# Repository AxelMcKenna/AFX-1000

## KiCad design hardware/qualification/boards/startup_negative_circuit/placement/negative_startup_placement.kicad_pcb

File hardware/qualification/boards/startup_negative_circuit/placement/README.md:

# NF03P native placement and routing study

This actual KiCad board places all231 parts from the sealed NF03C circuit on a
149×39 mm, four-layer PCB. It is a receiving design study, with no fabrication
release. `generated/native-pcb.json` records exact physical-pad/net parity,
including the four intentionally unconnected physical TLP4590AF lead3 pads.

The N12 force components are grouped on the left and N19 on the right. Deep
module/film parts are anchored explicitly. Thirty-two actual AUX-powered ICs
have assigned rear-side0603 bypass capacitors, with at most1.543 mm projected
pad separation before routing. Actual return/via inductance remains unaccepted.
The remaining generic shunt/timing/filter parts and physical connectors require
real selections and complete package/process review.

Six DCU0008A footprints use TI's actual example land instead of the generic
library's incompatible pad spacing. A separate cosmetic footprint variant
removes external silk triangles where they overlapped neighboring silk; it
preserves all electrical geometry. These changes are recorded with original and
replacement hashes. No DRC exclusions or ignored checks are used. The fresh
private `routing/connectivity-silk/input.kicad_pcb` has zero native violations,
but499 unrouted connections before the routing experiment.

The intended world frame is X=172+u, Z=3.5+v, Y=180.5−w, with nativeu/v on the
board and positivew outward from the component-front face. FR4 lies behind
that face; a1.76 mm maximum FR4 thickness and1.0 mm rear assembly envelope reach
Y183.26, below the Y183.8 lid seat. The receiving board spans X172..321 and
Z3.5..42.5. This arithmetic does not establish complete fit: actual bodies,
tails, mates, wire bends, bosses, mounting and floor-port blockage require the
separate whole-unit assembly review. There are no implemented board mounts.

`route_io.py` exports immutable per-candidate DSN/PCB/project files and imports
Specctra sessions while checking all component positions, sides, values and
pad nets. The In1.Cu AGND plane is a connectivity proposal. Default0.2 mm signal
tracks do not qualify the negative force path, Kelvin sensing or quiet returns;
these require explicit copper resistance, current and noise review after native
KiCad DRC. Existing E28 source/output Kelvin and force connections are separate
integration work.

The first FreeRouting native executable failed on missing Graal serialization
support; its log/rejection is retained under the private routing candidate.
The Java25/JAR fallback runs on the same bound DSN with a separate private
profile, analytics/API/MCP disabled. Router results require import and fresh
KiCad checks before adoption.

The newer [NF04R readiness successor](../ready_integration/README.md) adds an
output buffer and bypass and changes spare-gate wiring. This231-part board does
**not** yet implement that233-part circuit. Standalone ARM/START generation,
module initial-power margin, E28 integration, physical wiring, protected endpoint
voltage, startup/fault behavior and installed cooling remain open.

The SVG/PDF under `generated/` show actual footprint placement. They are review
drawings, not manufacturing outputs. All physical and release flags remain false.

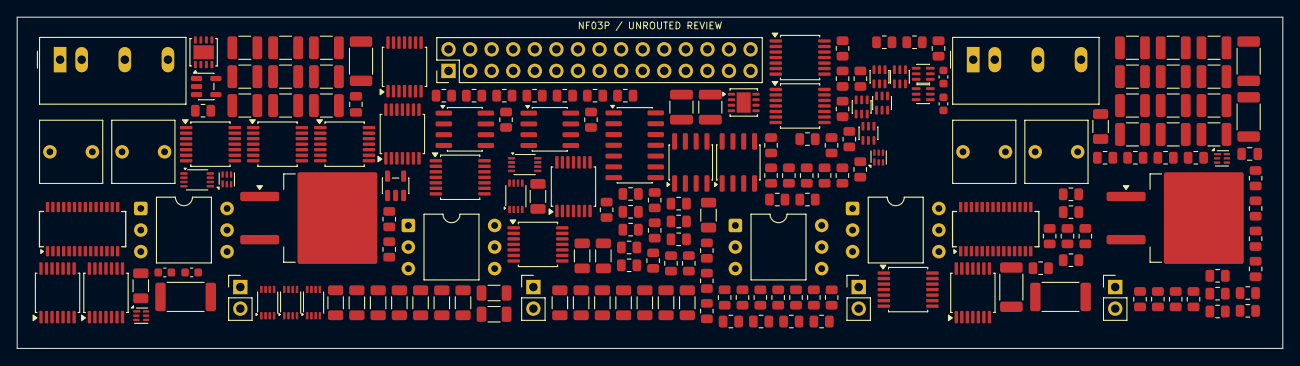
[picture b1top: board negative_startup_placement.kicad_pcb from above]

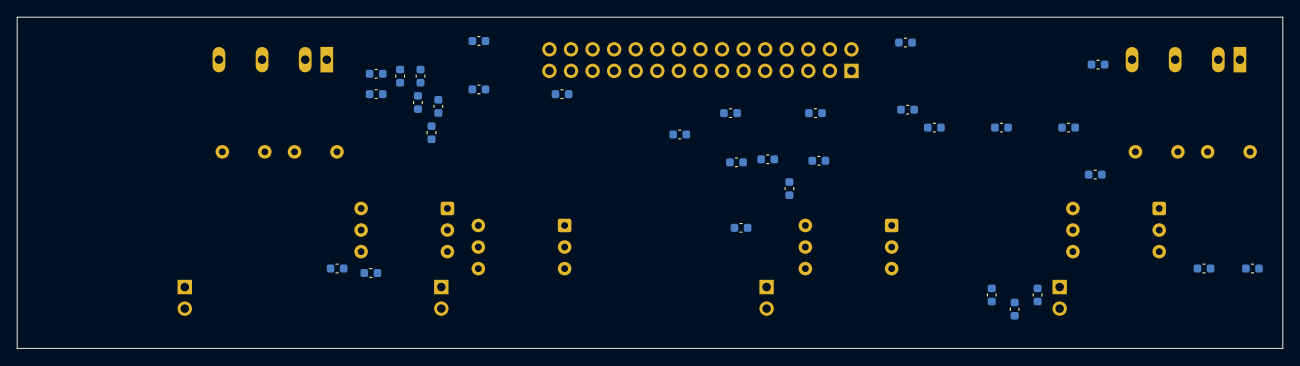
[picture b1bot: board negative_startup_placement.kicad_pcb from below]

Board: 4 copper layers, 149.0 x 39.0 mm, 231 parts (32 on the bottom side), 186 nets, no tracks yet.

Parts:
C1: 56nF C0G COMPLETE +/-10% RECEIVING; Capacitor_SMD__C_0805_2012Metric
C2: 33nF C0G COMPLETE +/-10% RECEIVING; Capacitor_SMD__C_0805_2012Metric
C3, C12, C39, C55, C56, C57, C58, C59, C60, C61, C62, C63, C64, C65, C66, C67, C68, C69, C70, C71, C72, C73, C74, C75, C76, C77, C78, C79, C80, C81, C82, C83, C84, C85, C86, C87: 100nF 50V X7R10% C0603C104K5RACTU - bypass effect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; Capacitor_SMD__C_0603_1608Metric
C4, C31: 10uF 25V X7R MODULE INPUT FILTER/EFFECTIVE/INRUSH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; Capacitor_SMD__C_1206_3216Metric
C5, C32: 1uF 50V X7R MODULE OUTPUT FILTER/EFFECTIVE HOLD; Capacitor_SMD__C_1206_3216Metric
C6, C33: 1uF 25V X7R LTC4261 local VIN effective HOLD; Capacitor_SMD__C_1206_3216Metric
C7, C9, C11, C13, C34, C36, C38, C40: 100nF 25V C0G C1206C104J3GACTU; Capacitor_SMD__C_1206_3216Metric
C8, C10, C35, C37: 10nF 50V C0G COMPLETE10% TIMING RECEIVING; Capacitor_SMD__C_1206_3216Metric
C14, C15, C16, C17, C18, C19, C20, C21, C22, C23, C24, C25, C41, C42, C43, C44, C45, C46, C47, C48, C49: 100nF 50V C0G C1210C104J5GACTU - COMPLETE10% RAMP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; Capacitor_SMD__C_1210_3225Metric
C26, C27, C50, C51: 2.2uF 63V PET5% MKS2C042201K00JSSD - COMPLETE10% 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; Capacitor_THT__C_Rect_L7.2mm_W7.2mm_P5.00mm_FKS2_FKP2_MKS2_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
C28, C30, C52, C54: 47nF 50V C0G C1206C473J5GACTU; Capacitor_SMD__C_1206_3216Metric
C29, C53: 100nF 50V C0G C1210C104J5GACTU; Capacitor_SMD__C_1210_3225Metric
J1: NEW NF03C CONTROL/KELVIN INTERFACE - physical con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; Connector_PinHeader_2.54mm__PinHeader_2x15_P2.54mm_Vertical
J2: N19 NEW FORCE IN/OUT - connector and harness unse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; Connector_PinHeader_2.54mm__PinHeader_1x02_P2.54mm_Vertical
J3: N19 E28 BANK GATE/COMMON CLAMP - physical interfa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; Connector_PinHeader_2.54mm__PinHeader_1x02_P2.54mm_Vertical
J4: N12 NEW FORCE IN/OUT - connector and harness unse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; Connector_PinHeader_2.54mm__PinHeader_1x02_P2.54mm_Vertical
J5: N12 E28 BANK GATE/COMMON CLAMP - physical interfa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; Connector_PinHeader_2.54mm__PinHeader_1x02_P2.54mm_Vertical
Q1, Q2: CSD19536KTT; Package_TO_SOT_SMD__TO-263-2
R1, R2, R8, R9: 10k; Resistor_SMD__R_0805_2012Metric
R3, R10: 47k; Resistor_SMD__R_0805_2012Metric
R4, R11: 383ohm COMPLETE +/-3% RECEIVING; Resistor_SMD__R_0805_2012Metric
R5, R12: 10k COMPLETE +/-3% RECEIVING; Resistor_SMD__R_0805_2012Metric
R6, R7, R13, R14: 220ohm COMPLETE +/-3% RECEIVING; Resistor_SMD__R_0805_2012Metric
R15, R16, R17, R18, R19, R20, R21, R22: 47k 3% TOTAL RECEIVING; Resistor_SMD__R_0805_2012Metric
R23: 160000ohm COMPLETE0.1% RECEIVING; Resistor_SMD__R_0805_2012Metric
R24, R41, R63, R65, R80, R82: 10k COMPLETE0.1% RECEIVING; Resistor_SMD__R_0805_2012Metric
R25, R49: 8660ohm COMPLETE0.1% RECEIVING; Resistor_SMD__R_0805_2012Metric
R26, R50: 35.7ohm COMPLETE0.1% RECEIVING; Resistor_SMD__R_0805_2012Metric
R27, R31, R35, R44, R47, R51: 100k COMPLETE0.1% RECEIVING; Resistor_SMD__R_0805_2012Metric
R28, R32, R36, R37, R38, R39, R45, R48, R52, R53, R54, R55, R59, R76: 10k COMPLETE3% RECEIVING; Resistor_SMD__R_0805_2012Metric
R29, R46: 2000ohm COMPLETE0.1% RECEIVING; Resistor_SMD__R_0805_2012Metric
R30: 40.2ohm COMPLETE0.1% RECEIVING; Resistor_SMD__R_0805_2012Metric
R33: 6040ohm COMPLETE0.1% RECEIVING; Resistor_SMD__R_0805_2012Metric
R34: 75ohm COMPLETE0.1% RECEIVING; Resistor_SMD__R_0805_2012Metric
R40: 102000ohm COMPLETE0.1% RECEIVING; Resistor_SMD__R_0805_2012Metric
R42: 10700ohm COMPLETE0.1% RECEIVING; Resistor_SMD__R_0805_2012Metric
R43: 169ohm COMPLETE0.1% RECEIVING; Resistor_SMD__R_0805_2012Metric
R56, R57, R73, R74: 392ohm 1% CRCW2010392RFKEF - COMPLETE3% RECEIVING; Resistor_SMD__R_2010_5025Metric
R58, R60, R61, R66, R67, R68, R75, R77, R78, R83, R84, R85: 47k COMPLETE3% RECEIVING; Resistor_SMD__R_0805_2012Metric
R62, R79: 30.4k COMPLETE0.1% RECEIVING; Resistor_SMD__R_0805_2012Metric
R64, R81: 78.7k COMPLETE0.1% RECEIVING; Resistor_SMD__R_0805_2012Metric
R69: 0.33ohm COMPLETE5% SHUNT RECEIVING; Resistor_SMD__R_2512_6332Metric
R70, R87: 10ohm COMPLETE3% RECEIVING; Resistor_SMD__R_0805_2012Metric
R71, R88: 1M; Resistor_SMD__R_0805_2012Metric
R72: 27ohm COMPLETE3% RECEIVING; Resistor_SMD__R_0805_2012Metric
R86: 0.12ohm COMPLETE5% SHUNT RECEIVING; Resistor_SMD__R_2512_6332Metric
R89: 39ohm COMPLETE3% RECEIVING; Resistor_SMD__R_0805_2012Metric
U1, U2, U7, U8: SN74AUP1G74DCUR; TI_DCU0008A
U3, U9: TPS3431SDRBR; Package_SON__VSON-8-1EP_3x3mm_P0.65mm_EP1.65x2.4mm
U4, U10: SN74LVC1G06DBVR; Package_TO_SOT_SMD__SOT-23-5_LocalSilk
U5, U6, U11, U12: TLP4590AF(F; Package_DIP__DIP-6_W10.16mm
U13: OPA2333AID; Package_SO__SOIC-8_3.9x4.9mm_P1.27mm
U14: TLV1822DR; Package_SO__SOIC-8_3.9x4.9mm_P1.27mm
U15: TLV1824DR; Package_SO__SOIC-14_3.9x8.7mm_P1.27mm
U16, U27: SN74LVC2T45DCUR; TI_DCU0008A
U17, U22: TMR 1-1215; Converter_DCDC__Converter_DCDC_TRACO_TMR-1-xxxx_Single_THT
U18, U23: LTC4261IGN#PBF; Package_SO__SSOP-28_3.9x9.9mm_P0.635mm
U19, U24: ISO7721FDR; Package_SO__SOIC-8_3.9x4.9mm_P1.27mm
U20, U21, U25, U26: TPS389001DSET; Package_SON__WSON-6_1.5x1.5mm_P0.5mm
U28, U29, U30, U31, U32, U33, U34: SN74AUP2G14DCKR; Package_TO_SOT_SMD__SOT-363_SC-70-6_LocalSilk
U35, U36, U37, U38, U39, U40, U41, U42, U43, U44: SN74HCS08PWR; Package_SO__TSSOP-14_4.4x5mm_P0.65mm
U45, U46: SN74HCS32PWR; Package_SO__TSSOP-14_4.4x5mm_P0.65mm
U47, U48: SN74HCS14PWR; Package_SO__TSSOP-14_4.4x5mm_P0.65mm

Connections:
AGND: C1.2, C2.2, C3.2, C4.2, C12.2, C31.2, C39.2, C55.2, C56.2, C57.2, C58.2, C59.2, C60.2, C61.2, C62.2, C63.2, C64.2, C65.2, C66.2, C67.2, C68.2, C69.2, C70.2, C71.2, C72.2, C73.2, C74.2, C75.2, C76.2, C77.2, C78.2, C79.2, C80.2, C81.2, C82.2, C83.2, C84.2, C85.2, C86.2, C87.2, J1.2, R3.2, R10.2, R15.2, R16.2, R17.2, R18.2, R19.2, R20.2, R21.2, R22.2, R27.2, R31.2, R35.2, R44.2, R47.2, R51.2, R59.2, R61.2, R67.2, R68.2, R76.2, R78.2, R84.2, R85.2, U1.4, U2.4, U3.4, U3.9, U4.3, U7.4, U8.4, U9.4, U9.9, U10.3, U13.3, U13.4, U13.5, U14.4, U15.12, U16.4, U17.1, U19.5, U22.1, U24.5, U27.4, U28.2, U29.2, U30.2, U31.2, U32.2, U33.2, U34.2, U35.7, U36.7, U37.7, U38.7, U39.7, U40.7, U41.7, U42.7, U43.7, U44.7, U44.9, U44.10, U44.12, U44.13, U45.7, U46.7, U46.9, U46.10, U46.12, U46.13, U47.7, U48.3, U48.5, U48.7, U48.9, U48.11, U48.13
AUX2V6: C56.1, C57.1, C58.1, C59.1, C60.1, C61.1, C62.1, C63.1, C64.1, C65.1, C66.1, C67.1, C68.1, C69.1, C70.1, C71.1, C72.1, C73.1, C74.1, C75.1, C76.1, C77.1, C78.1, C79.1, C80.1, C81.1, C82.1, C83.1, C84.1, C85.1, C86.1, C87.1, J1.1, R1.1, R2.1, R8.1, R9.1, R37.1, R38.1, R39.1, R53.1, R54.1, R55.1, U1.7, U1.8, U2.2, U2.7, U2.8, U3.1, U7.7, U7.8, U8.2, U8.7, U8.8, U9.1, U13.8, U14.8, U15.3, U16.1, U16.5, U27.8, U28.5, U29.5, U30.5, U31.5, U32.5, U33.5, U34.5, U35.14, U36.14, U37.14, U38.14, U39.14, U40.14, U41.14, U42.14, U43.14, U44.14, U45.14, U46.14, U47.14, U48.14
AUX_VALID: J1.5, R16.1, U35.1
DIG5_FORCE: C3.1, C12.1, C39.1, C55.1, J1.3, R4.1, R11.1, U4.5, U10.5, U16.8, U19.8, U24.8, U27.1, U27.5
E28_COMBINED_FAULT_REQUEST: J1.14, U34.4
E28_COMBINED_FAULT_REQUEST_BUFFER_MID: U34.3, U34.6
E28_COMBINED_FAULT_REQUEST_HCS: U34.1, U46.6
E28_NATIVE_FAULT_REQUEST: J1.13, U46.4
E28_NOT_FAULT: J1.15, R22.1, U44.4
GLOBAL_MASTER: J1.6, R15.1, U35.2
GLOBAL_VALID: U35.3, U35.5, U37.4, U38.5, U38.13, U40.12, U41.13
GUARDED_12V_FORCE: C4.1, C31.1, J1.4, U17.2, U22.2
N12_ARM: J1.24, R20.1, U30.1
N12_ARM_CONDITIONED: U30.4, U38.12, U39.1, U39.4, U40.13, U41.12
N12_ARM_CONDITIONED_BUFFER_MID: U30.3, U30.6
N12_BANK_CLAMP_GATE: R14.2, U12.4
N12_BANK_COMMON: J5.2, U12.6
N12_BANK_GATE: J5.1, R14.1
N12_BIAS_CT: C37.1, U25.5
N12_BIAS_HOST5: R84.1, U24.6, U27.3
N12_BIAS_RESET_N: R83.2, U24.3, U25.6, U26.6
N12_BIAS_SENSE: R79.2, R80.1, U25.1
N12_BIAS_VALID: J1.17, R85.1, U27.6, U43.13
N12_CG_SERIES: C52.1, R87.2
N12_CLAMPS_RELEASE: J1.28, R10.1, U10.2, U33.4
N12_CLAMPS_RELEASE_BUFFER_MID: U33.3, U33.6
N12_CLAMPS_RELEASE_HCS: U33.1, U42.3
N12_CLAMP_LED_A: R11.2, R12.1, U11.1
N12_CLAMP_LED_K: R12.2, U10.4, U12.2
N12_CLAMP_LED_MID: U11.2, U12.1
N12_COMPLETE: J1.27, U8.5, U39.12
N12_COMPLETE_CLK: U8.1, U41.8
N12_COMPLETE_CLR_N: U8.6, U41.11
N12_CONTROLLER_ON: R77.1, U23.2, U24.2
N12_CR_TOP: C41.1, C42.1, C43.1, C44.1, C45.1, C46.1, C47.1, C48.1, C49.1, R89.2
N12_CWD: C2.1, U9.2
N12_DRAIN_SENSE: R88.2, U23.16
N12_E28_SRC: C41.2, C42.2, C43.2, C44.2, C45.2, C46.2, C47.2, C48.2, C49.2, J4.2, Q2.2, R88.1
N12_F0: U45.8, U45.12
N12_FAULT_REQUEST: J1.26, U45.11, U46.2
N12_FEED_MID: R73.2, R74.1
N12_F_OUTPUT: U39.11, U45.13
N12_F_SOURCE: U39.3, U45.9
N12_F_TIMEOUT: U39.8, U45.10
N12_F_WD_ARM: U39.6, U39.9
N12_INTVCC: C34.1, C36.1, C38.1, C40.1, R79.1, R83.1, U23.5, U23.6, U23.7, U23.8, U23.9, U23.22, U24.1, U25.3, U25.4, U26.3, U26.4
N12_ISO24: C32.1, R73.1, U22.4
N12_NOT_COMPLETE: U8.3, U9.5
N12_NOT_PERMIT: U7.3, U9.6
N12_NOT_READY: U39.13, U47.10
N12_NOT_SAFE: U39.2, U47.8
N12_NOT_WDO: U39.10, U47.12
N12_OUTPUT_OV_GOOD: R55.2, U15.13, U43.10, U44.2
N12_OUTPUT_UV_GOOD: R54.2, U15.14, U44.1
N12_OUT_INV: R41.1, R45.1, R48.1, U13.7
N12_OUT_OV_REF: R46.2, R47.1, U15.11
N12_OUT_OV_SENSE: R48.2, U15.10
N12_OUT_SUM: R40.2, R41.2, U13.6
N12_OUT_UV_REF: R43.2, R44.1, U15.8
N12_OUT_UV_RMID: R42.2, R43.1
N12_OUT_UV_SENSE: R45.2, U15.9
N12_OV_OK: J1.10, U43.5
N12_OV_SENSE: J1.12, R52.1
N12_P03_SRC: C32.2, C33.2, C34.2, C35.2, C36.2, C37.2, C38.2, C40.2, C50.2, C51.2, C52.2, C53.2, C54.2, J4.1, R75.2, R76.1, R77.2, R80.2, R82.2, R86.1, U22.6, U23.1, U23.3, U23.10, U23.11, U23.13, U23.23, U23.24, U23.25, U23.26, U23.27, U24.4, U25.2, U26.2
N12_PASS_CLAMP_GATE: R13.2, U11.4
N12_PASS_GATE: Q2.1, R13.1, R87.1, U23.15
N12_PASS_SOURCE: Q2.3, R86.2, U11.6, U23.14
N12_PCLR0: U40.11, U41.1, U42.1
N12_PCLR1: U41.3, U41.4
N12_PERMIT: U7.5, U16.3, U41.9
N12_PERMIT_CLR_N: U7.6, U41.6
N12_PERMIT_D: U7.2, U40.8
N12_PROTECTED: J1.29, R40.1
N12_RAMP: C50.1, C51.1, R89.1, U23.18
N12_READY: U41.10, U44.3, U47.11
N12_RUN_HOST5: R78.1, U16.6, U24.7
N12_SAFE: U40.5, U41.5, U43.11, U47.9
N12_SOURCE_SAFE0: U43.6, U43.9
N12_SOURCE_SAFE1: U43.8, U43.12
N12_SOURCE_UV_GOOD: R53.2, U14.7, U43.4
N12_SOURCE_UV_REF: R50.2, R51.1, U14.6
N12_SOURCE_UV_RMID: R49.2, R50.1
N12_SOURCE_UV_SENSE: R52.2, U14.5
N12_SS: C53.1, U23.19
N12_START: J1.25, R21.1, U31.1
N12_START_ARMED: U40.3, U40.4
N12_START_CONDITIONED: U7.1, U31.4
N12_START_CONDITIONED_BUFFER_MID: U31.3, U31.6
N12_START_SAFE: U40.6, U40.9
N12_TMR: C54.1, U23.20
N12_VIN: C33.1, R74.2, R75.1, R81.1, U23.21
N12_VIN_VALID_CT: C35.1, U26.5
N12_VIN_VALID_SENSE: R81.2, R82.1, U26.1
N12_WDO: R8.2, U9.7, U40.2, U47.13
N12_WD_ARMED: R9.2, U9.8, U39.5, U40.1
N12_WD_ENABLE: U9.3, U38.11
N19_ARM: J1.18, R18.1, U28.1
N19_ARM_CONDITIONED: U28.4, U35.4, U35.9, U35.12, U37.5, U38.4
N19_ARM_CONDITIONED_BUFFER_MID: U28.3, U28.6
N19_BANK_CLAMP_GATE: R7.2, U6.4
N19_BANK_COMMON: J3.2, U6.6
N19_BANK_GATE: J3.1, R7.1
N19_BIAS_CT: C10.1, U20.5
N19_BIAS_HOST5: R67.1, U19.6, U27.2
N19_BIAS_RESET_N: R66.2, U19.3, U20.6, U21.6
N19_BIAS_SENSE: R62.2, R63.1, U20.1
N19_BIAS_VALID: J1.16, R68.1, U27.7, U42.13
N19_CG_SERIES: C28.1, R70.2
N19_CLAMPS_RELEASE: J1.22, R3.1, U4.2, U32.4
N19_CLAMPS_RELEASE_BUFFER_MID: U32.3, U32.6
N19_CLAMPS_RELEASE_HCS: U32.1, U38.8
N19_CLAMP_LED_A: R4.2, R5.1, U5.1
N19_CLAMP_LED_K: R5.2, U4.4, U6.2
N19_CLAMP_LED_MID: U5.2, U6.1
N19_COMPLETE: J1.21, U2.5, U36.4
N19_COMPLETE_CLK: U2.1, U38.3
N19_COMPLETE_CLR_N: U2.6, U38.6
N19_CONTROLLER_ON: R60.1, U18.2, U19.2
N19_CR_TOP: C14.1, C15.1, C16.1, C17.1, C18.1, C19.1, C20.1, C21.1, C22.1, C23.1, C24.1, C25.1, R72.2
N19_CWD: C1.1, U3.2
N19_DRAIN_SENSE: R71.2, U18.16
N19_E28_SRC: C14.2, C15.2, C16.2, C17.2, C18.2, C19.2, C20.2, C21.2, C22.2, C23.2, C24.2, C25.2, J2.2, Q1.2, R71.1
N19_F0: U45.3, U45.4
N19_FAULT_REQUEST: J1.20, U45.6, U46.1
N19_FEED_MID: R56.2, R57.1
N19_F_OUTPUT: U36.6, U45.5
N19_F_SOURCE: U35.8, U45.1
N19_F_TIMEOUT: U36.3, U45.2
N19_F_WD_ARM: U35.11, U36.1
N19_INTVCC: C7.1, C9.1, C11.1, C13.1, R62.1, R66.1, U18.5, U18.6, U18.7, U18.8, U18.9, U18.22, U19.1, U20.3, U20.4, U21.3, U21.4
N19_ISO24: C5.1, R56.1, U17.4
N19_NOT_COMPLETE: U2.3, U3.5
N19_NOT_PERMIT: U1.3, U3.6
N19_NOT_READY: U36.5, U47.4
N19_NOT_SAFE: U35.10, U47.2
N19_NOT_WDO: U36.2, U47.6
N19_OUTPUT_OV_GOOD: R39.2, U15.1, U42.10, U43.2
N19_OUTPUT_UV_GOOD: R38.2, U15.2, U43.1
N19_OUT_INV: R24.1, R28.1, R32.1, U13.1
N19_OUT_OV_REF: R30.2, R31.1, U15.7
N19_OUT_OV_RMID: R29.2, R30.1
N19_OUT_OV_SENSE: R32.2, U15.6
N19_OUT_SUM: R23.2, R24.2, U13.2
N19_OUT_UV_REF: R26.2, R27.1, U15.4
N19_OUT_UV_RMID: R25.2, R26.1
N19_OUT_UV_SENSE: R28.2, U15.5
N19_OV_OK: J1.9, U42.5
N19_OV_SENSE: J1.11, R36.1
N19_P03_SRC: C5.2, C6.2, C7.2, C8.2, C9.2, C10.2, C11.2, C13.2, C26.2, C27.2, C28.2, C29.2, C30.2, J2.1, R58.2, R59.1, R60.2, R63.2, R65.2, R69.1, U17.6, U18.1, U18.3, U18.10, U18.11, U18.13, U18.23, U18.24, U18.25, U18.26, U18.27, U19.4, U20.2, U21.2
N19_PASS_CLAMP_GATE: R6.2, U5.4
N19_PASS_GATE: Q1.1, R6.1, R70.1, U18.15
N19_PASS_SOURCE: Q1.3, R69.2, U5.6, U18.14
N19_PCLR0: U37.6, U37.9, U38.9
N19_PCLR1: U37.8, U37.12
N19_PERMIT: U1.5, U16.2, U38.1
N19_PERMIT_CLR_N: U1.6, U37.11
N19_PERMIT_D: U1.2, U37.3
N19_PROTECTED: J1.23, R23.1
N19_RAMP: C26.1, C27.1, R72.1, U18.18
N19_READY: U38.2, U43.3, U47.3
N19_RUN_HOST5: R61.1, U16.7, U19.7
N19_SAFE: U36.13, U37.13, U42.11, U47.1
N19_SOURCE_SAFE0: U42.6, U42.9
N19_SOURCE_SAFE1: U42.8, U42.12
N19_SOURCE_UV_GOOD: R37.2, U14.1, U42.4
N19_SOURCE_UV_REF: R34.2, R35.1, U14.2
N19_SOURCE_UV_RMID: R33.2, R34.1
N19_SOURCE_UV_SENSE: R36.2, U14.3
N19_SS: C29.1, U18.19
N19_START: J1.19, R19.1, U29.1
N19_START_ARMED: U36.8, U36.12
N19_START_CONDITIONED: U1.1, U29.4
N19_START_CONDITIONED_BUFFER_MID: U29.3, U29.6
N19_START_SAFE: U36.11, U37.1
N19_TMR: C30.1, U18.20
N19_VIN: C6.1, R57.2, R58.1, R64.1, U18.21
N19_VIN_VALID_CT: C8.1, U21.5
N19_VIN_VALID_SENSE: R64.2, R65.1, U21.1
N19_WDO: R1.2, U3.7, U36.10, U47.5
N19_WD_ARMED: R2.2, U3.8, U35.13, U36.9
N19_WD_ENABLE: U3.3, U35.6
NF_FAULT_REQUEST: U46.3, U46.5, U48.1
NF_NO_FAULT: U37.2, U37.10, U38.10, U40.10, U41.2, U42.2, U44.6
NOT_NF_FAULT_REQUEST: U44.5, U48.2
PROTECT_REF: J1.8, R25.1, R29.1, R33.1, R42.1, R46.1, R49.1
RESET_REQUEST: J1.7, R17.1

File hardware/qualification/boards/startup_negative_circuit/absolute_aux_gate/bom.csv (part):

Reference,Part_or_value,Footprint,Source,Note
U1,SN74AUP1G74DCUR,NF05H_Manufacturer:TI_DCU0008A,https://www.ti.com/lit/ds/symlink/sn74aup1g74.pdf,
U2,SN74AUP1G74DCUR,NF05H_Manufacturer:TI_DCU0008A,https://www.ti.com/lit/ds/symlink/sn74aup1g74.pdf,
U3,TPS3431SDRBR,Package_SON:VSON-8-1EP_3x3mm_P0.65mm_EP1.65x2.4mm,https://www.ti.com/lit/ds/symlink/tps3431.pdf,
C1,56nF50V C0G5% C1206C563J5GACTU - COMPLETE10% RECEIVING,Capacitor_SMD:C_1206_3216Metric,https://content.kemet.com/datasheets/KEM_C1003_C0G_SMD.pdf,
R1,10k,Resistor_SMD:R_0805_2012Metric,,
R2,10k,Resistor_SMD:R_0805_2012Metric,,
U4,SN74LVC1G06DBVR,Package_TO_SOT_SMD:SOT-23-5,https://www.ti.com/lit/ds/symlink/sn74lvc1g06.pdf,AUX-powered sink: actual input VIH1.7 over2.3..2.7V; 5.5V-tolerant OD output. Full powered leakage remains receiving.
R3,205000ohm 0.1% TNPW0805205KBEEA - COMPLETE3% RECEIVING,Resistor_SMD:R_0805_2012Metric,https://www.vishay.com/docs/28758/tnpw_e3.pdf,
R4,402ohm 0.1% TNPW0805402RBEEA - COMPLETE3% RECEIVING,Resistor_SMD:R_0805_2012Metric,https://www.vishay.com/docs/28758/tnpw_e3.pdf,
R5,10k COMPLETE +/-3% RECEIVING,Resistor_SMD:R_0805_2012Metric,,
R6,220ohm COMPLETE +/-3% RECEIVING,Resistor_SMD:R_0805_2012Metric,,
U5,TLP4590AF(F,Package_DIP:DIP-6_W10.16mm,https://toshiba.semicon-storage.com/info/docget.jsp?did=7053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,"FormB normally CLOSED at LED0. A-connection4/6; gate-current/time/hot leakage are RECEIVING requirements, not qualified"
R7,220ohm COMPLETE +/-3% RECEIVING,Resistor_SMD:R_0805_2012Metric,,
U6,TLP4590AF(F,Package_DIP:DIP-6_W10.16mm,https://toshiba.semicon-storage.com/info/docget.jsp?did=7053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,"FormB normally CLOSED at LED0. A-connection4/6; gate-current/time/hot leakage are RECEIVING requirements, not qualified"
U7,SN74AUP1G74DCUR,NF05H_Manufacturer:TI_DCU0008A,https://www.ti.com/lit/ds/symlink/sn74aup1g74.pdf,
U8,SN74AUP1G74DCUR,NF05H_Manufacturer:TI_DCU0008A,https://www.ti.com/lit/ds/symlink/sn74aup1g74.pdf,
U9,TPS3431SDRBR,Package_SON:VSON-8-1EP_3x3mm_P0.65mm_EP1.65x2.4mm,https://www.ti.com/lit/ds/symlink/tps3431.pdf,
C2,33nF50V C0G5% C1206C333J5GACTU - COMPLETE10% RECEIVING,Capacitor_SMD:C_1206_3216Metric,https://content.kemet.com/datasheets/KEM_C1003_C0G_SMD.pdf,
R8,10k,Resistor_SMD:R_0805_2012Metric,,
R9,10k,Resistor_SMD:R_0805_2012Metric,,
U10,SN74LVC1G06DBVR,Package_TO_SOT_SMD:SOT-23-5,https://www.ti.com/lit/ds/symlink/sn74lvc1g06.pdf,AUX-powered sink: actual input VIH1.7 over2.3..2.7V; 5.5V-tolerant OD output. Full powered leakage remains receiving.
R10,205000ohm 0.1% TNPW0805205KBEEA - COMPLETE3% RECEIVING,Resistor_SMD:R_0805_2012Metric,https://www.vishay.com/docs/28758/tnpw_e3.pdf,
R11,402ohm 0.1% TNPW0805402RBEEA - COMPLETE3% RECEIVING,Resistor_SMD:R_0805_2012Metric,https://www.vishay.com/docs/28758/tnpw_e3.pdf,
R12,10k COMPLETE +/-3% RECEIVING,Resistor_SMD:R_0805_2012Metric,,
R13,220ohm COMPLETE +/-3% RECEIVING,Resistor_SMD:R_0805_2012Metric,,
U11,TLP4590AF(F,Package_DIP:DIP-6_W10.16mm,https://toshiba.semicon-storage.com/info/docget.jsp?did=7053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,"FormB normally CLOSED at LED0. A-connection4/6; gate-current/time/hot leakage are RECEIVING requirements, not qualified"
R14,220ohm COMPLETE +/-3% RECEIVING,Resistor_SMD:R_0805_2012Metric,,
U12,TLP4590AF(F,Package_DIP:DIP-6_W10.16mm,https://toshiba.semicon-storage.com/info/docget.jsp?did=7053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,"FormB normally CLOSED at LED0. A-connection4/6; gate-current/time/hot leakage are RECEIVING requirements, not qualified"
J1,NEW NF03C CONTROL/KELVIN INTERFACE - physical connector unselected,Connector_PinHeader_2.54mm:PinHeader_2x15_P2.54mm_Vertical,,"Pin contract only. Real force/control connectors, guard faults, return and harness not implemented; no TEST J3 use."
R15,47k 3% TOTAL RECEIVING,Resistor_SMD:R_0805_2012Metric,,
R16,47k 3% TOTAL RECEIVING,Resistor_SMD:R_0805_2012Metric,,
R17,47k 3% TOTAL RECEIVING,Resistor_SMD:R_0805_2012Metric,,
R18,47k 3% TOTAL RECEIVING,Resistor_SMD:R_0805_2012Metric,,
R19,47k 3% TOTAL RECEIVING,Resistor_SMD:R_0805_2012Metric,,
R20,47k 3% TOTAL RECEIVING,Resistor_SMD:R_0805_2012Metric,,
R21,47k 3% TOTAL RECEIVING,Resistor_SMD:R_0805_2012Metric,,
R22,47k 3% TOTAL RECEIVING,Resistor_SMD:R_0805_2012Metric,,
U13,OPA2333AID,Package_SO:SOIC-8_3.9x4.9mm_P1.27mm,https://www.ti.com/lit/ds/symlink/opa333.pdf,
R23,160000ohm COMPLETE0.1% RECEIVING,Resistor_SMD:R_0805_2012Metric,,
R24,10k COMPLETE0.1% RECEIVING,Resistor_SMD:R_0805_2012Metric,,
R25,8660ohm COMPLETE0.1% RECEIVING,Resistor_SMD:R_0805_2012Metric,,
R26,35.7ohm COMPLETE0.1% RECEIVING,Resistor_SMD:R_0805_2012Metric,,
R27,100k COMPLETE0.1% RECEIVING,Resistor_SMD:R_0805_2012Metric,,
R28,10k COMPLETE3% RECEIVING,Resistor_SMD:R_0805_2012Metric,,
R29,2000ohm COMPLETE0.1% RECEIVING,Resistor_SMD:R_0805_2012Metric,,
R30,40.2ohm COMPLETE0.1% RECEIVING,Resistor_SMD:R_0805_2012Metric,,
R31,100k COMPLETE0.1% RECEIVING,Resistor_SMD:R_0805_2012Metric,,
R32,10k COMPLETE3% RECEIVING,Resistor_SMD:R_0805_2012Metric,,
R33,6040ohm COMPLETE0.1% RECEIVING,Resistor_SMD:R_0805_2012Metric,,
R34,75ohm COMPLETE0.1% RECEIVING,Resistor_SMD:R_0805_2012Metric,,
R35,100k COMPLETE0.1% RECEIVING,Resistor_SMD:R_0805_2012Metric,,
R36,10k COMPLETE3% RECEIVING,Resistor_SMD:R_0805_2012Metric,,
R37,10k COMPLETE3% RECEIVING,Resistor_SMD:R_0805_2012Metric,,
R38,10k COMPLETE3% RECEIVING,Resistor_SMD:R_0805_2012Metric,,
R39,10k COMPLETE3% RECEIVING,Resistor_SMD:R_0805_2012Metric,,
R40,102000ohm COMPLETE0.1% RECEIVING,Resistor_SMD:R_0805_2012Metric,,
R41,10k COMPLETE0.1% RECEIVING,Resistor_SMD:R_0805_2012Metric,,
R42,10700ohm COMPLETE0.1% RECEIVING,Resistor_SMD:R_0805_2012Metric,,
R43,169ohm COMPLETE0.1% RECEIVING,Resistor_SMD:R_0805_2012Metric,,
R44,100k COMPLETE0.1% RECEIVING,Resistor_SMD:R_0805_2012Metric,,
R45,10k COMPLETE3% RECEIVING,Resistor_SMD:R_0805_2012Metric,,
R46,2000ohm COMPLETE0.1% RECEIVING,Resistor_SMD:R_0805_2012Metric,,
R47,100k COMPLETE0.1% RECEIVING,Resistor_SMD:R_0805_2012Metric,,
R48,10k COMPLETE3% RECEIVING,Resistor_SMD:R_0805_2012Metric,,
R49,8660ohm COMPLETE0.1% RECEIVING,Resistor_SMD:R_0805_2012Metric,,
R50,35.7ohm COMPLETE0.1% RECEIVING,Resistor_SMD:R_0805_2012Metric,,
R51,100k COMPLETE0.1% RECEIVING,Resistor_SMD:R_0805_2012Metric,,
R52,10k COMPLETE3% RECEIVING,Resistor_SMD:R_0805_2012Metric,,
R53,10k COMPLETE3% RECEIVING,Resistor_SMD:R_0805_2012Metric,,
R54,10k COMPLETE3% RECEIVING,Resistor_SMD:R_0805_2012Metric,,
R55,10k COMPLETE3% RECEIVING,Resistor_SMD:R_0805_2012Metric,,
U14,TLV1822DR,Package_SO:SOIC-8_3.9x4.9mm_P1.27mm,https://www.ti.com/lit/ds/symlink/tlv1821.pdf,
U15,TLV1824DR,Package_SO:SOIC-14_3.9x8.7mm_P1.27mm,https://www.ti.com/lit/ds/symlink/tlv1821.pdf,
U16,SN74LVC2T45DCUR,NF05H_Manufacturer:TI_DCU0008A,https://www.ti.com/lit/ds/symlink/sn74lvc2t45.pdf,
C3,100nF 50V X7R10% C0603C104K5RACTU - bypass effective/PDN HOLD,Capacitor_SMD:C_0603_1608Metric,,
J2,N19 NEW FORCE IN/OUT - connector and harness unselected,Connector_PinHeader_2.54mm:PinHeader_1x02_P2.54mm_Vertical,,"Series before existing E28 J1 receiving force pin, not a sense-wire power path. No contact rating accepted."
J3,N19 E28 BANK GATE/COMMON CLAMP - physical interface unselected,Connector_PinHeader_2.54mm:PinHeader_1x02_P2.54mm_Vertical,,
U17,TMR 1-1215,Converter_DCDC:Converter_DCDC_TRACO_TMR-1-xxxx_Single_THT,https://www.tracopower.com/sites/default/files/products/data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,
C4,10uF 25V X7R MODULE INPUT FILTER/EFFECTIVE/INRUSH HOLD,Capacitor_SMD:C_1206_3216Metric,,
C5,1uF 50V X7R MODULE OUTPUT FILTER/EFFECTIVE HOLD,Capacitor_SMD:C_1206_3216Metric,,
R56,402ohm 1% CRCW2010402RFKEF - COMPLETE3% RECEIVING,Resistor_SMD:R_2010_5025Metric,https://www.vishay.com/docs/20035/dcrcwe3.pdf,
R57,402ohm 1% CRCW2010402RFKEF - COMPLETE3% RECEIVING,Resistor_SMD:R_2010_5025Metric,https://www.vishay.com/docs/20035/dcrcwe3.pdf,
R58,47k COMPLETE3% RECEIVING,Resistor_SMD:R_0805_2012Metric,,
R59,10k COMPLETE3% RECEIVING,Resistor_SMD:R_0805_2012Metric,,Explicit discharge path; negative source current counted.
R60,47k COMPLETE3% RECEIVING,Resistor_SMD:R_0805_2012Metric,,
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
